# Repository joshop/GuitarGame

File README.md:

# GuitarGame
DELTARUNE's guitar rhythm game in electronic form using an STM32 microcontroller.
KiCAD EDA files are in the top level directory. `firmware/` contains the code.

## Design
- An STM32C071FBP6 microcontroller is at the core.
- Power is supplied from a 4.2V LiPo, managed using a BQ21040, or a USB-C port, via an LDO.
- Four 74HC594 shift registers are used to control the LEDs.
- Two piezo speakers are driven by the STM32 to produce audio.
- Two capacitive touch pads are driven through 1 megaohm resistors.

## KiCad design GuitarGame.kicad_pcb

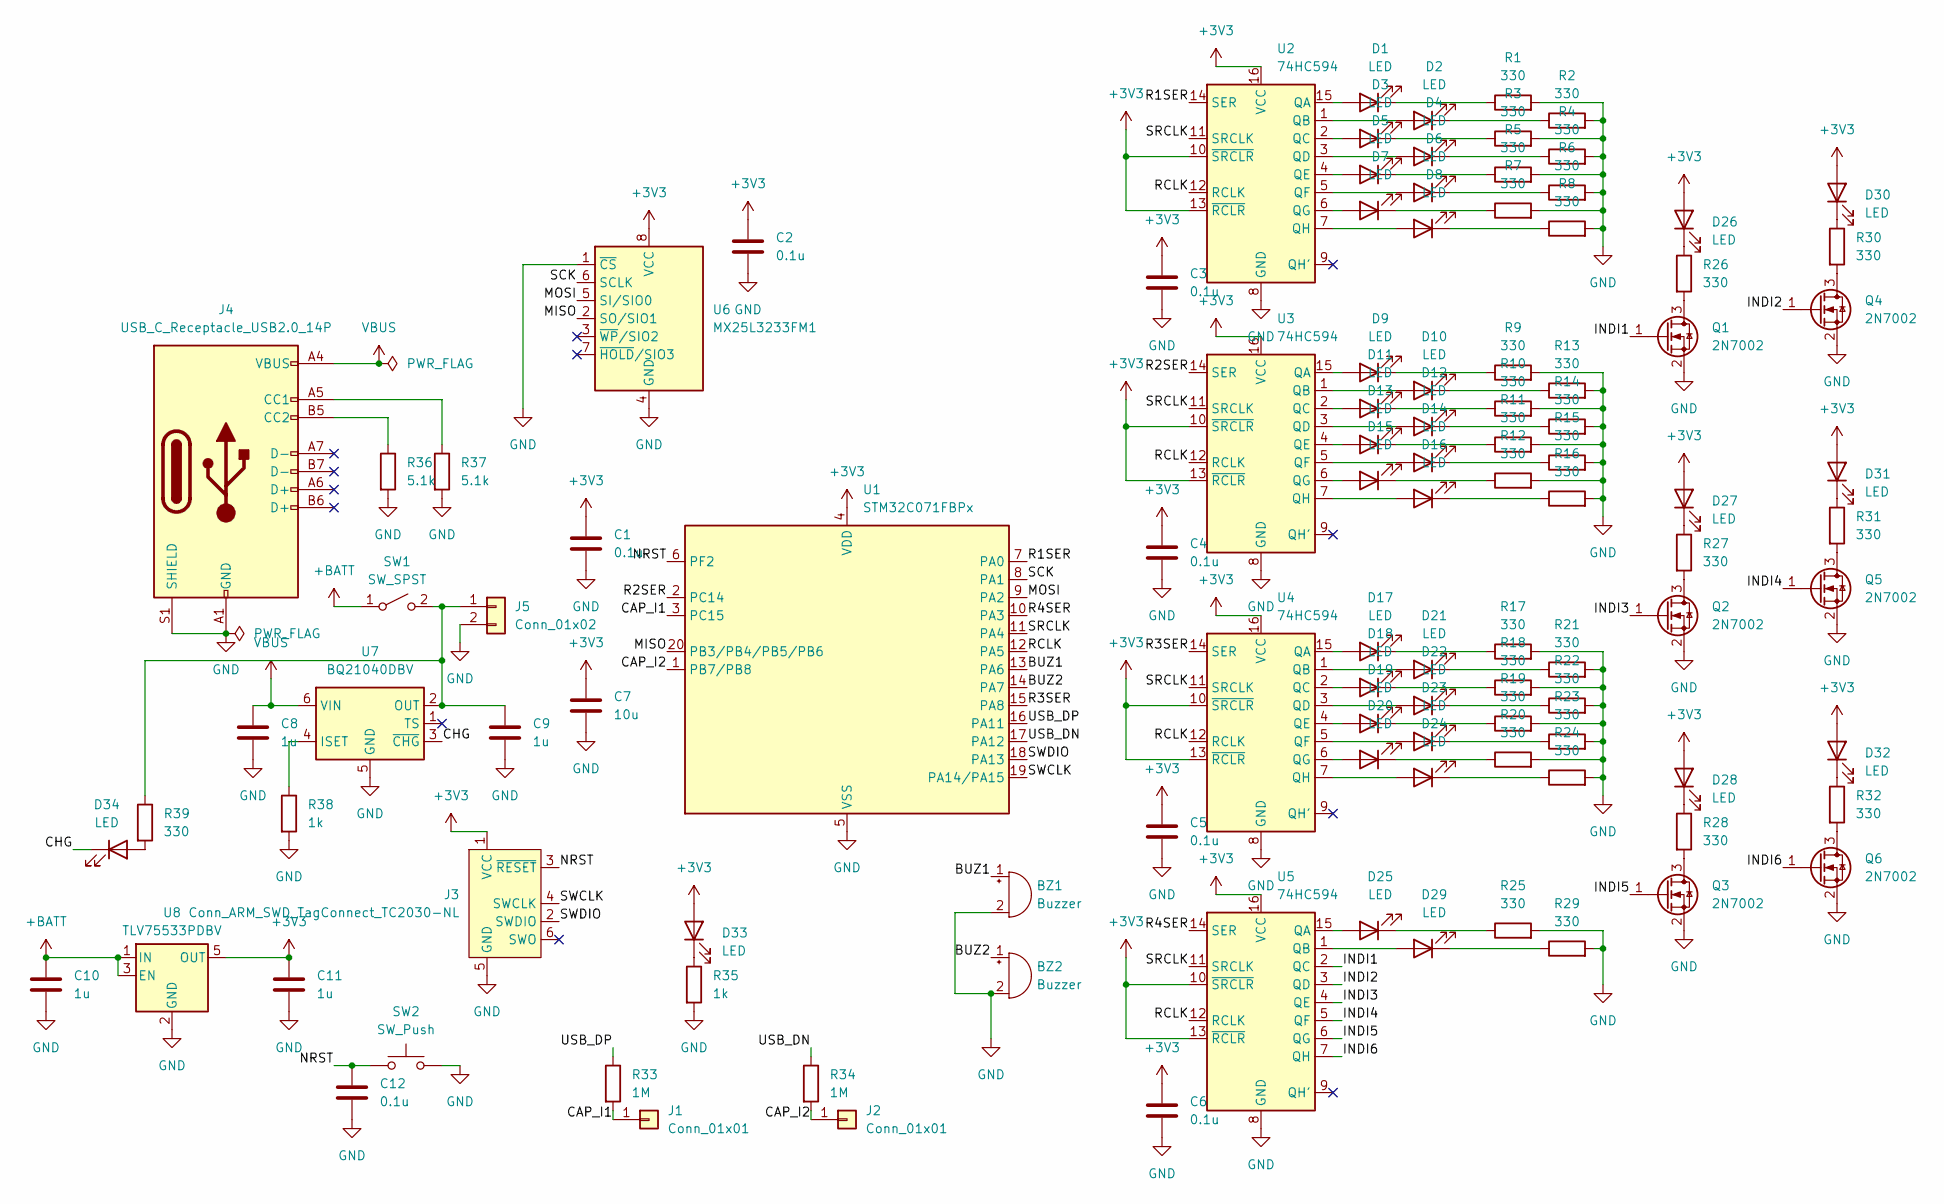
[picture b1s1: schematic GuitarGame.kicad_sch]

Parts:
BZ1, BZ2: Buzzer; Buzzer_12x9.5RM7.6
C1, C2, C3, C4, C5, C6, C12: 0.1u; C_0603_1608Metric
C7: 10u; C_0603_1608Metric
C8, C9, C10, C11: 1u; C_0603_1608Metric
D1, D2, D3, D4, D5, D6: LED; LED_0805_2012Metric
D7, D8, D9, D10, D11, D12, D13, D14, D15, D16, D17, D18, D19, D20, D21, D22, D23, D24, D25, D29: LED; LED_0603_1608Metric
D26, D27, D28, D30, D31, D32: LED; LED_1206_3216Metric
D33, D34: LED; C_0603_1608Metric
J1, J2: Conn_01x01; cap_pad
J3: Conn_ARM_SWD_TagConnect_TC2030-NL; Tag-Connect_TC2030-IDC-NL_2x03_P1.27mm_Vertical
J4: USB_C_Receptacle_USB2.0_14P; USB_C_Receptacle_GCT_USB4110
J5: Conn_01x02; JST_PH_B2B-PH-K_1x02_P2.00mm_Vertical
Q1, Q2, Q3, Q4, Q5, Q6: 2N7002; SOT-23
R1, R2, R3, R4, R5, R6, R7, R8, R9, R10, R11, R12, R13, R14, R15, R16, R17, R18, R19, R20, R21, R22, R23, R24, R25, R26, R27, R28, R29, R30, R31, R32, R39: 330; R_0603_1608Metric
R33, R34: 1M; R_0603_1608Metric
R35, R38: 1k; R_0603_1608Metric
R36, R37: 5.1k; R_0603_1608Metric
SW1: SW_SPST; SW_Slide_SPDT_Straight_CK_OS102011MS2Q
SW2: SW_Push; SW_Push_1P1T_NO_CK_KSC7xxJ
U1: STM32C071FBPx; TSSOP-20_4.4x6.5mm_P0.65mm
U2, U3, U4, U5: 74HC594; SOIC-16_3.9x9.9mm_P1.27mm
U6: MX25L3233FM1; JEITA_SOIC-8_3.9x4.9mm_P1.27mm
U7: BQ21040DBV; SOT-23-6
U8: TLV75533PDBV; SOT-23-5

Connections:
+BATT: C10.1, SW1.1 (A), U8.1 (IN), U8.3 (EN)
/BUZ1: BZ1.1 (+), U1.13 (PA6)
/BUZ2: BZ2.1 (+), U1.14 (PA7)
/CAP_I1: J1.1, R33.2, U1.3 (PC15)
/CAP_I2: J2.1, R34.2, U1.1 (PB7/PB8)
/CHG: D34.1 (K), U7.3 (~CHG)
/INDI1: Q1.1 (G), U5.2 (QC)
/INDI2: Q4.1 (G), U5.3 (QD)
/INDI3: Q2.1 (G), U5.4 (QE)
/INDI4: Q5.1 (G), U5.5 (QF)
/INDI5: Q3.1 (G), U5.6 (QG)
/INDI6: Q6.1 (G), U5.7 (QH)
/MISO: U1.20 (PB3/PB4/PB5/PB6), U6.2 (SO/SIO1)
/MOSI: U1.9 (PA2), U6.5 (SI/SIO0)
/NRST: C12.1, J3.3 (~RESET), SW2.1, U1.6 (PF2)
/R1SER: U1.7 (PA0), U2.14 (SER)
/R2SER: U1.2 (PC14), U3.14 (SER)
/R3SER: U1.15 (PA8), U4.14 (SER)
/R4SER: U1.10 (PA3), U5.14 (SER)
/RCLK: U1.12 (PA5), U2.12 (RCLK), U3.12 (RCLK), U4.12 (RCLK), U5.12 (RCLK)
/SCK: U1.8 (PA1), U6.6 (SCLK)
/SRCLK: U1.11 (PA4), U2.11 (SRCLK), U3.11 (SRCLK), U4.11 (SRCLK), U5.11 (SRCLK)
/SWCLK: J3.4 (SWCLK), U1.19 (PA14/PA15)
/SWDIO: J3.2 (SWDIO), U1.18 (PA13)
/USB_DN: R34.1, U1.17 (PA12)
/USB_DP: R33.1, U1.16 (PA11)
GND: BZ1.2 (-), BZ2.2 (-), C1.2, C2.2, C3.2, C4.2, C5.2, C6.2, C7.2, C8.2, C9.2, C10.2, C11.2, C12.2, J3.5 (GND), J4.A1 (GND), J4.A12 (GND), J4.B1 (GND), J4.B12 (GND), J4.S1 (SHIELD), J5.2, Q1.2 (S), Q2.2 (S), Q3.2 (S), Q4.2 (S), Q5.2 (S), Q6.2 (S), R1.2, R2.2, R3.2, R4.2, R5.2, R6.2, R7.2, R8.2, R9.2, R10.2, R11.2, R12.2, R13.2, R14.2, R15.2, R16.2, R17.2, R18.2, R19.2, R20.2, R21.2, R22.2, R23.2, R24.2, R25.2, R29.2, R35.2, R36.2, R37.2, R38.2, SW2.2, U1.5 (VSS), U2.8 (GND), U3.8 (GND), U4.8 (GND), U5.8 (GND), U6.1 (~CS), U6.4 (GND), U7.5 (GND), U8.2 (GND)
unnamed: D1.2 (A), U2.15 (QA)
unnamed: D1.1 (K), R1.1
unnamed: D2.2 (A), U2.1 (QB)
unnamed: D2.1 (K), R2.1
unnamed: D3.2 (A), U2.2 (QC)
unnamed: D3.1 (K), R3.1
unnamed: D4.2 (A), U2.3 (QD)
unnamed: D4.1 (K), R4.1
unnamed: D5.2 (A), U2.4 (QE)
unnamed: D5.1 (K), R5.1
unnamed: D6.2 (A), U2.5 (QF)
unnamed: D6.1 (K), R6.1
unnamed: D7.2 (A), U2.6 (QG)
unnamed: D7.1 (K), R7.1
unnamed: D8.2 (A), U2.7 (QH)
unnamed: D8.1 (K), R8.1
unnamed: D9.2 (A), U3.15 (QA)
unnamed: D9.1 (K), R9.1
unnamed: D10.2 (A), U3.1 (QB)
unnamed: D10.1 (K), R13.1
unnamed: D11.2 (A), U3.2 (QC)
unnamed: D11.1 (K), R10.1
unnamed: D12.2 (A), U3.3 (QD)
unnamed: D12.1 (K), R14.1
unnamed: D13.2 (A), U3.4 (QE)
unnamed: D13.1 (K), R11.1
unnamed: D14.2 (A), U3.5 (QF)
unnamed: D14.1 (K), R15.1
unnamed: D15.2 (A), U3.6 (QG)
unnamed: D15.1 (K), R12.1
unnamed: D16.2 (A), U3.7 (QH)
unnamed: D16.1 (K), R16.1
unnamed: D17.2 (A), U4.15 (QA)
unnamed: D17.1 (K), R17.1
unnamed: D18.2 (A), U4.2 (QC)
unnamed: D18.1 (K), R18.1
unnamed: D19.2 (A), U4.4 (QE)
unnamed: D19.1 (K), R19.1
unnamed: D20.2 (A), U4.6 (QG)
unnamed: D20.1 (K), R20.1
unnamed: D21.2 (A), U4.1 (QB)
unnamed: D21.1 (K), R21.1
unnamed: D22.2 (A), U4.3 (QD)
unnamed: D22.1 (K), R22.1
unnamed: D23.2 (A), U4.5 (QF)
unnamed: D23.1 (K), R23.1
unnamed: D24.2 (A), U4.7 (QH)
unnamed: D24.1 (K), R24.1
unnamed: D25.2 (A), U5.15 (QA)
unnamed: D25.1 (K), R25.1
unnamed: D26.1 (K), R26.1
unnamed: D27.1 (K), R27.1
unnamed: D28.1 (K), R28.1
unnamed: D29.2 (A), U5.1 (QB)
unnamed: D29.1 (K), R29.1
unnamed: D30.1 (K), R30.1
unnamed: D31.1 (K), R31.1
unnamed: D32.1 (K), R32.1
unnamed: D33.1 (K), R35.1
unnamed: D34.2 (A), R39.2
unnamed: J4.A5 (CC1), R37.1
unnamed: J4.B5 (CC2), R36.1
unnamed: Q1.3 (D), R26.2
unnamed: Q2.3 (D), R27.2
unnamed: Q3.3 (D), R28.2
unnamed: Q4.3 (D), R30.2
unnamed: Q5.3 (D), R31.2
unnamed: Q6.3 (D), R32.2
unnamed: R38.1, U7.4 (ISET)
VBUS: C8.1, J4.A4 (VBUS), J4.A9 (VBUS), J4.B4 (VBUS), J4.B9 (VBUS), U7.6 (VIN)

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
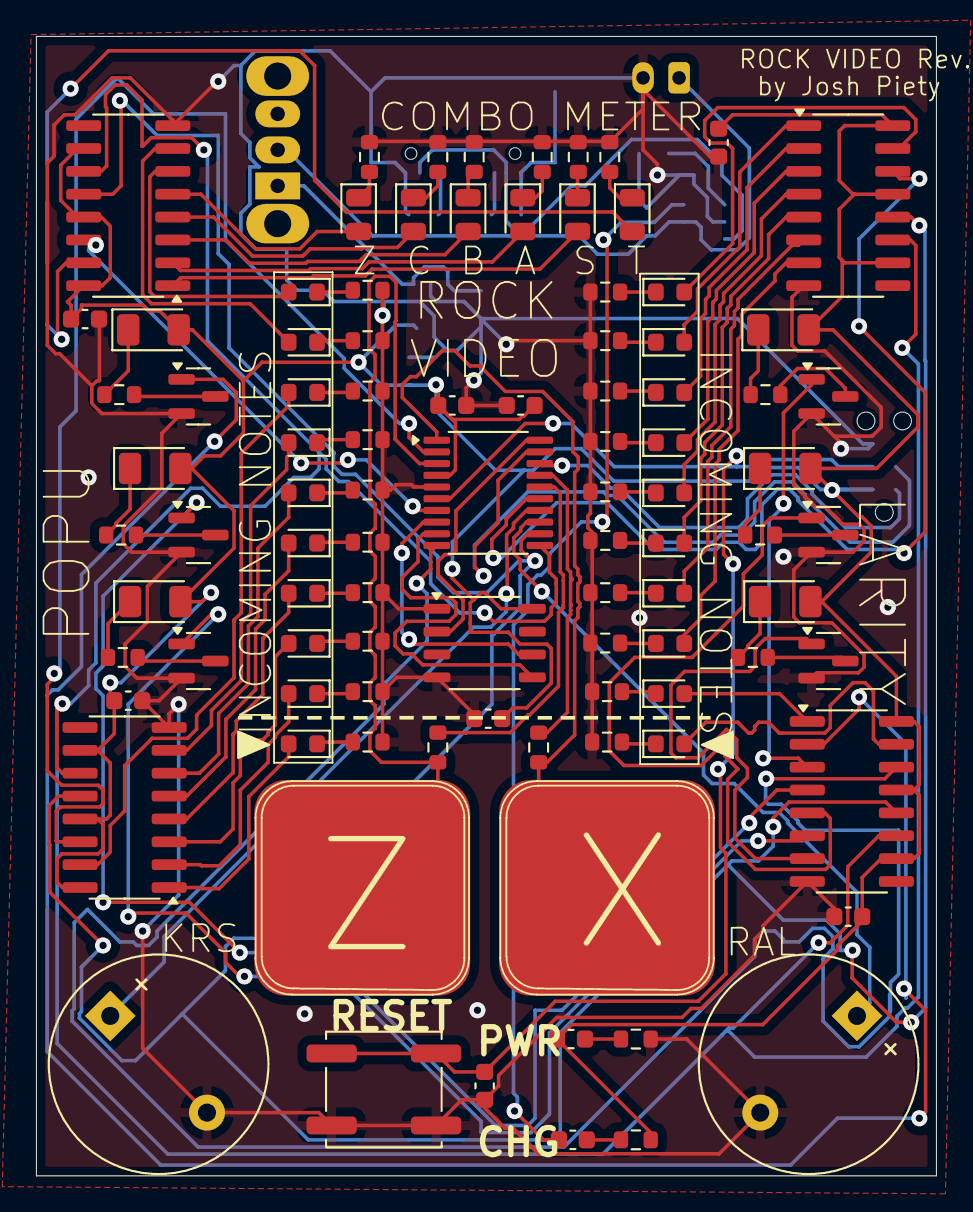
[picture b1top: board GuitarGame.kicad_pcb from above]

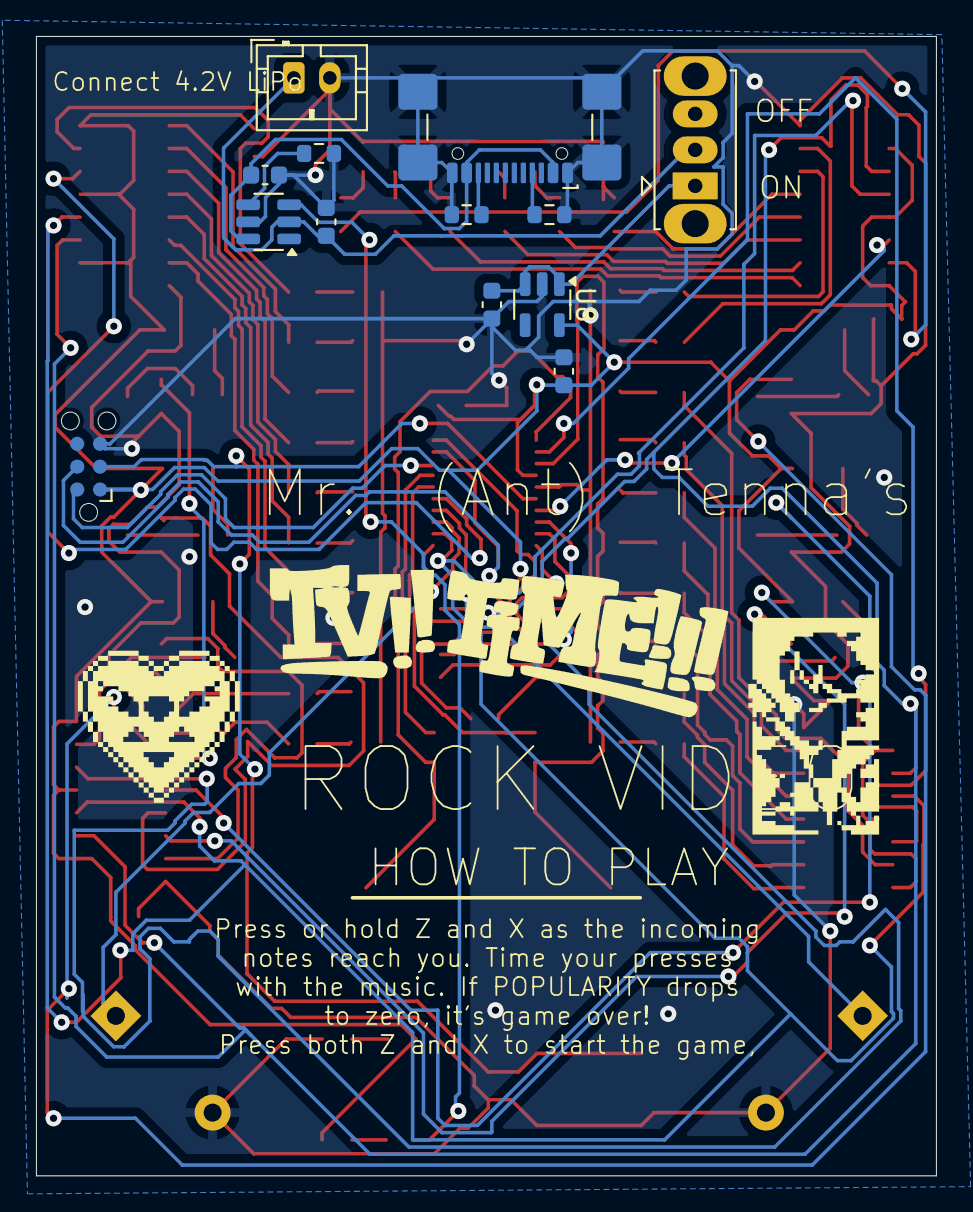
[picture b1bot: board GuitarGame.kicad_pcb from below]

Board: 2 copper layers, 50.0 x 63.3 mm, 108 parts (13 on the bottom side), 99 nets.

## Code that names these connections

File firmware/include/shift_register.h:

#pragma once

#include "stm32c0xx_hal.h"

/*  R1SER -> PA0
 *  R2SER -> PC14
 *  R3SER -> PA8
 *  R4SER -> PA3
 *  SRCLK -> PA4
 *  RCLK  -> PA5
 */

#define GPIO_R1SER GPIOA, GPIO_PIN_0
#define GPIO_R2SER GPIOC, GPIO_PIN_14
#define GPIO_R3SER GPIOA, GPIO_PIN_8
#define GPIO_R4SER GPIOA, GPIO_PIN_3
#define GPIO_SRCLK GPIOA, GPIO_PIN_4
#define GPIO_RCLK GPIOA, GPIO_PIN_5

// void shift_all(uint32_t state);
extern volatile uint8_t pwm_buffer[32];
extern volatile uint8_t pwm_threshold;
void shift_all();
void shiftreg_init();

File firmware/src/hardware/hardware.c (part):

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                        GPIO_PIN_8 | GPIO_PIN_11 | GPIO_PIN_12,
                    GPIO_PIN_RESET);

  /*Configure GPIO pin : PB7 */
  GPIO_InitStruct.Pin = GPIO_PIN_7;
  GPIO_InitStruct.Mode = GPIO_MODE_INPUT;
  GPIO_InitStruct.Pull = GPIO_NOPULL;
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  GPIO_InitStruct.Pull = GPIO_NOPULL;
  HAL_GPIO_Init(GPIOA, &GPIO_InitStruct);

  /*Configure GPIO pin : PC14 */
  GPIO_InitStruct.Pin = GPIO_PIN_14;
  GPIO_InitStruct.Mode = GPIO_MODE_OUTPUT_PP;
  GPIO_InitStruct.Pull = GPIO_NOPULL;
  GPIO_InitStruct.Speed = GPIO_SPEED_FREQ_LOW;
  HAL_GPIO_Init(GPIOC, &GPIO_InitStruct);

  /*Configure GPIO pins : PA0 PA3 PA4 PA5
   *                           PA8 PA11 PA12 */
  GPIO_InitStruct.Pin = GPIO_PIN_0 | GPIO_PIN_3 | GPIO_PIN_4 | GPIO_PIN_5 |
                        GPIO_PIN_8 | GPIO_PIN_12;
  GPIO_InitStruct.Mode = GPIO_MODE_OUTPUT_PP;
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
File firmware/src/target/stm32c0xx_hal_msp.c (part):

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    __HAL_RCC_GPIOA_CLK_ENABLE();
    __HAL_RCC_GPIOB_CLK_ENABLE();
    /**SPI1 GPIO Configuration
     *    PA1     ------> SPI1_SCK
     *    PA2     ------> SPI1_MOSI
     *    PB4     ------> SPI1_MISO
     */
    GPIO_InitStruct.Pin = GPIO_PIN_1 | GPIO_PIN_2;
    GPIO_InitStruct.Mode = GPIO_MODE_AF_PP;
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    __HAL_RCC_SPI1_CLK_DISABLE();

    /**SPI1 GPIO Configuration
     *    PA1     ------> SPI1_SCK
     *    PA2     ------> SPI1_MOSI
     *    PB4     ------> SPI1_MISO
     */
    HAL_GPIO_DeInit(GPIOA, GPIO_PIN_1 | GPIO_PIN_2);

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
    __HAL_RCC_GPIOA_CLK_ENABLE();
    /**TIM3 GPIO Configuration
     *    PA6     ------> TIM3_CH1
     */
    GPIO_InitStruct.Pin = GPIO_PIN_6;
    GPIO_InitStruct.Mode = GPIO_MODE_AF_PP;
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
    __HAL_RCC_GPIOA_CLK_ENABLE();
    /**TIM17 GPIO Configuration
     * PA7     ------> TIM17_CH1
     */
    GPIO_InitStruct.Pin = GPIO_PIN_7;
    GPIO_InitStruct.Mode = GPIO_MODE_AF_PP;
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
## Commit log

2025-09-20 Import EDA + firmware
2025-09-25 Add images
2025-09-25 Add more images
2025-09-25 Make images smaller

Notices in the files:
firmware/src/target/stm32c0xx_hal_msp.c:
Copyright (c) 2025 STMicroelectronics.
All rights reserved.
This software is licensed under terms that can be found in the LICENSE file
